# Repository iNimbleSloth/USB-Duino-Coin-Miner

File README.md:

# USB-Duino-Coin-Miner

Duino Coin is a crypto currency that can be mined on low powered devices such as an Arduino Uno.

This project is a USB Duino Coin Miner that required a host computer to run the minning application on. The more USB miners used, the more mining power is available.

In the project you will find KiCAD files for the schematic and PCB layout.

Main	(Main Repository)<br>
	|<br>
	Duino_Coin_Miner_SMD_v1.1	(KiCAD6 project folder for surfacemount ATmega miner)<br>
	|<br>
	Duino_Coin_Miner_THT_V1.1	(KiCAD6 project folder for though-hole ATmega miner)<br>
	|<br>
	License<br>
	|<br>
	README.md
<br>
<br>
Looking for a quick and easy solution? You can purchase the PCBs directly from PCBWay.com without the need to install KiCAD.<br>
https://www.pcbway.com/project/shareproject/USB_Duino_Coin_Miner_SMD_26c9c008.html<br>
https://www.pcbway.com/project/shareproject/USB_Duino_Coin_Miner_THT_20c1372f.html<br>
Get 5$ credit when signing up at PCBWay - https://www.pcbway.com/setinvite.aspx?inviteid=417998<br>

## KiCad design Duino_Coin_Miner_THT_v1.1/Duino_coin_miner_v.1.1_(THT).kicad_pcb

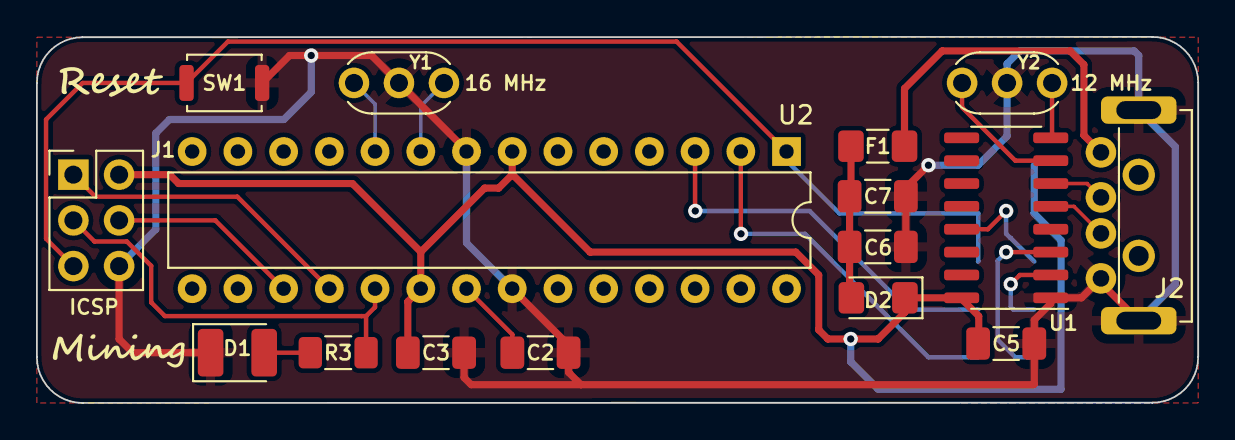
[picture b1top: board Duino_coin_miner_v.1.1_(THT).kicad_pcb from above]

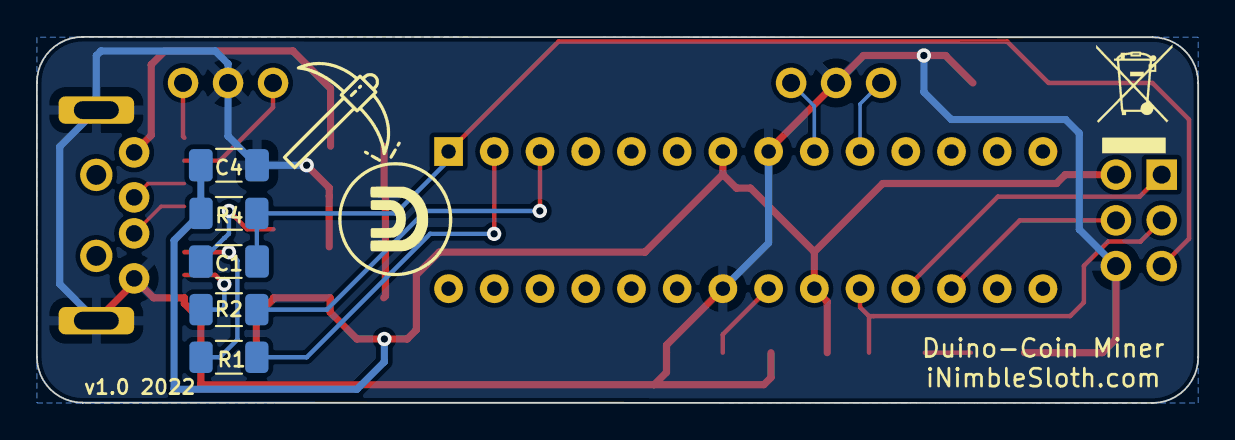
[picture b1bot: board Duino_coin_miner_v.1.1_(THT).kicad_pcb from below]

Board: 2 copper layers, 64.5 x 20.3 mm, 21 parts (5 on the bottom side), 21 nets.

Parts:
C1, C2, C5, C6: 100nF; C_1206_3216Metric_Pad1.33x1.80mm_HandSolder
C3, C4, C7: 4.7uF; C_1206_3216Metric_Pad1.33x1.80mm_HandSolder
D1: LED - Yellow; LED_1210_3225Metric_Pad1.42x2.65mm_HandSolder
D2: SS1P3L; D_1206_3216Metric_Pad1.42x1.75mm_HandSolder
F1: Polyfuse; Fuse_1206_3216Metric_Pad1.42x1.75mm_HandSolder
J1: Conn_02x03_Odd_Even; PinHeader_2x03_P2.54mm_Vertical
J2: USB_A; USB_A Plug
R1, R2, R3, R4: 1k; R_1206_3216Metric_Pad1.30x1.75mm_HandSolder
SW1: SW_Push; SW_Push_SPST_NO_Alps_SKRK
U1: CH340G; SOIC-16_3.9x9.9mm_P1.27mm
U2: ATmega328-P; DIP-28_W7.62mm
Y1: 16 MHz; Resonator-3Pin_W6.0mm_H3.0mm
Y2: 12 MHz; Resonator-3Pin_W6.0mm_H3.0mm

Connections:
/16mhz+: U2.9 (XTAL1/PB6), Y1.3
/16mhz-: U2.10 (XTAL2/PB7), Y1.1
/D+: J2.3 (D+), U1.5 (UD+)
/D-: J2.2 (D-), U1.6 (UD-)
GND: C2.1, C3.1, C4.1, C5.1, C6.1, C7.1, D1.1 (K), J1.6, J2.4 (GND), J2.5 (Shield), SW1.2, U1.1 (GND), U2.8 (GND), U2.22 (GND), Y1.2, Y2.2
MISO: J1.1, U2.18 (PB4)
MOSI: J1.4, U2.17 (PB3)
unnamed: C1.1, U1.13 (~DTR)
unnamed: C2.2, U2.21 (AREF)
unnamed: D1.2 (A), R3.2
unnamed: F1.1, J2.1 (VBUS)
unnamed: R1.1, U2.2 (PD0)
unnamed: R2.1, U2.3 (PD1)
unnamed: U1.7 (XI), Y2.1
unnamed: U1.8 (XO), Y2.3
RESET: C1.2, J1.5, R4.1, SW1.1, U2.1 (~RESET/PC6)
RX: R1.2, U1.3 (RXD)
SCK: J1.3, R3.1, U2.19 (PB5)
TX: R2.2, U1.2 (TXD)
VCC: C3.2, C4.2, C5.2, D2.1 (K), J1.2, R4.2, U1.16 (VCC), U2.7 (VCC), U2.20 (AVCC)
VUSB: C6.2, C7.2, D2.2 (A), F1.2

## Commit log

2022-09-05 SMD version added
2022-09-05 Miners uploaded
